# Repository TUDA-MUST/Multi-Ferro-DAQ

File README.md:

# Multi-Ferro-DAQ

**Wearable 8-channel charge amplifier and data acquisition system for piezo- and ferroelectric sensors.**

The system reads up to **8 charge sources simultaneously** via **two RJ45 connectors** (4 sensors per connector).
The PCB is designed for **mobile use**: it can be strapped to a test person, runs on **battery power**, and streams data in **millivolts (mV)** via **Wi-Fi** at up to **2000 samples per second**.

---

## 📋 Specifications

| Parameter | Value |
|---|---|
| Hardware revision | v1.4 |
| Channels | 8, simultaneously sampled |
| ADC | TI ADS131E08, 24 bit ΔΣ, programmable gain G = 1, 2, 4, 8, 12 |
| Charge amplifier | AD8608 (quad CMOS op-amp), one per channel |
| Feedback network | C_F = 680 pF (C0G, ±5 %) ∥ R_F = 1 GΩ (±10 %) |
| Sensitivity | 1 / C_F ≈ 1.47 mV/pC |
| Time constant / lower cut-off | τ = R_F · C_F = 0.68 s → f_c = 1 / (2π τ) ≈ 0.23 Hz |
| Output range (vs. V_bias) | ±2.5 V at G = 1, ±4 V / G for G ≥ 2 |
| Charge range | ±1.70 nC at G = 1 (fault flag above ±2.375 V ≈ ±1.62 nC) |
| Sample rate | 1–2 kSa/s recommended (ADC supports up to 64 kSa/s, but samples are lost above 2 kSa/s) |
| Microcontroller | ESP32-S3-MINI-1-N8 |
| Data interface | Wi-Fi 2.4 GHz access point, TCP port 8080 |
| Power | 1S Li-ion/LiPo (protected cell, JST-PH) or USB-C; on-board charger ≈ 336 mA |
| On-board supplies | 5 V analog (LM2775 charge pump), 3.3 V digital (TPS7A91 LDO), V_bias = 2.5 V |
| Extras | 6-axis IMU (ICM-42670-P), 2 RGB status LEDs, board-level RF shield over the analog front end |
| PCB | 4 layers, 50 mm × 65 mm |

---

## ⚙️ How it works

```mermaid
flowchart LR
    S["Sensors<br/>2 × RJ45, 4 each"] --> CA["8 × charge amplifier<br/>AD8608<br/>C_F = 680 pF ∥ R_F = 1 GΩ"]
    VB["V_bias = 2.5 V<br/>TLV9051 buffer"] --> CA
    VB --> ADC
    CA --> ADC["ADS131E08<br/>8 ch, 24 bit, simultaneous"]
    ADC -- "SPI + DRDY" --> MCU["ESP32-S3"]
    MCU -- "Wi-Fi, TCP :8080" --> PC["Client<br/>MATLAB / MMM"]
    IMU["IMU ICM-42670-P"] -.-> MCU
```

**Analog front end.** The board runs from a single 5 V analog supply. To process bipolar charge signals, all analog circuitry is referenced to a mid-supply voltage **V_bias = 2.5 V**. V_bias is generated by the ADS131E08's internal op-amp and buffered by a TLV9051. Each channel is an inverting charge amplifier: the non-inverting input is tied to V_bias, the inverting input is the summing node the sensor connects to, and C_F ∥ R_F form the feedback. R_F provides the DC path that keeps the output from drifting, and sets the lower cut-off frequency.

**Digitization.** The ADS131E08 samples all eight amplifier outputs simultaneously and measures each one differentially against V_bias, so the result is the amplifier's output voltage relative to mid-supply. The analog front end and the ADC sit under a board-level RF shield.

**Firmware.** The ESP32-S3 uses both cores. An interrupt on the ADC's DRDY signal reads each sample into a queue. A second task converts the raw values to mV, removes the selected PGA gain, and sends packets of 64 samples to the client over TCP.

**Power.** The board runs from a 1S Li-ion/LiPo cell or USB-C. A TP4056 charges the cell from USB. An LM2775 charge pump supplies the 5 V analog rail, and a TPS7A91 low-noise LDO supplies the 3.3 V digital rail.

---

## 🧮 Converting the output to charge

The firmware streams each channel as the amplifier output voltage U (in mV, relative to V_bias, with the PGA gain already removed).
For signal frequencies well above the cut-off f_c ≈ 0.23 Hz, the charge Q delivered by the sensor into the amplifier input is

$$Q = -C_F \cdot U$$

With C_F = 680 pF:

$$Q\,[\mathrm{pC}] = -0.68 \cdot U\,[\mathrm{mV}]$$

Example: U = 100 mV → Q = −68 pC. The amplifier is inverting, so the sign of the output is opposite to the sign of the charge flowing into the input.

The feedback resistor makes the amplifier a high-pass. A charge step decays as e^(−t/τ) with τ = 0.68 s: after 0.68 s only 37 % of the step remains, and after 3.4 s (5τ) less than 1 %. For slow or quasi-static signals, correct for this with the transfer function

$$H(f) = -\frac{1}{C_F} \cdot \frac{j 2\pi f \tau}{1 + j 2\pi f \tau}$$

---

## 🔌 Sensor connection (RJ45 pinout)

Each RJ45 port carries four sensors. Each sensor uses one wire pair: the solid-colored wire goes to the amplifier input (**signal, +**), the striped wire to **V_bias (−)**. Pin numbers follow the jack. Wire colors are given for both T-568A and T-568B, the two wiring schemes for Ethernet cables defined in ANSI/TIA-568. They differ only in that the orange and green pairs are swapped; T-568B is the more common one for commercial installations and patch cables in North America. In both, all odd pins are V_bias (striped wire) and all even pins are signal (solid wire).

**By ADC channel:**

| Port I | Port II | + (signal) pin | T-568A | T-568B | − (V_bias) pin | T-568A | T-568B |
|---|---|---|---|---|---|---|---|
| CHAN1 | CHAN5 | 8 | brown | brown | 7 | white-brown | white-brown |
| CHAN2 | CHAN6 | 6 | orange | green | 3 | white-orange | white-green |
| CHAN3 | CHAN7 | 2 | green | orange | 1 | white-green | white-orange |
| CHAN4 | CHAN8 | 4 | blue | blue | 5 | white-blue | white-blue |

**By RJ45 pin:**

| Pin | Wire (T-568A) | Wire (T-568B) | Port I | Port II |
|---|---|---|---|---|
| 1 | white-green | white-orange | CHAN3 − | CHAN7 − |
| 2 | green | orange | CHAN3 + | CHAN7 + |
| 3 | white-orange | white-green | CHAN2 − | CHAN6 − |
| 4 | blue | blue | CHAN4 + | CHAN8 + |
| 5 | white-blue | white-blue | CHAN4 − | CHAN8 − |
| 6 | orange | green | CHAN2 + | CHAN6 + |
| 7 | white-brown | white-brown | CHAN1 − | CHAN5 − |
| 8 | brown | brown | CHAN1 + | CHAN5 + |

> **Important:** the V_bias pins sit at **2.5 V above board ground**. Never connect them to GND or to the cable shield. Shorting V_bias to ground loads the reference and drives the channels into saturation. Use the RJ45 shield for the cable screen. It connects to the board's shield net.

The pinout is also printed on the PCB silkscreen (T-568B colors).

---

## 🛠️ Building the hardware

1. **Order the PCB with assembly** (e.g. JLCPCB) using the files in [`PCB/jlcpcb/production_files`](PCB/jlcpcb/production_files): Gerber archive, BOM and CPL.
   - 4-layer board, stackup JLC041611-3313, 1 oz inner copper (see `PCB/jlcpcb/Added Info.txt`).
2. **Order separately** (not part of the assembly BOM):
   - Laird **BMI-S-204-C** RF shield cover.
   - A **protected** 1S Li-ion/LiPo cell with a JST-PH 2-pin plug. The on-board TP4056 charger has no cell protection.
   - RJ45 cables or adapters for your sensors.
3. **After assembly:**
   - Press the shield cover onto the soldered J7 frame.
   - Check the solder jumpers. The factory states are listed in the BOM documentation.
   - Connect the battery and flash the firmware (see below).

The complete bill of materials, with manufacturer part numbers, key specs and datasheet links, is in [`PCB/BOM`](PCB/BOM/README.md) ([CSV](PCB/BOM/BOM_Multi-Ferro-DAQ_v1.4.csv)). The design files require **KiCad 10**. All project-specific symbols, footprints and 3D models are in `PCB/components`.

---

## ⚡ Flashing the firmware

The ESP32-S3 is flashed with the Arduino IDE using
`Software/ADC_readout/ardu_adc_dual_core_wifi_tcp/ardu_adc_dual_core_wifi_tcp.ino`.
The sketch includes the driver from `Software/ADC_readout/lib/`, so keep the folder structure intact.

**Required:**
- Arduino-ESP32 core (Espressif), installed via the Boards Manager
- FastLED library
- ArduinoJson library (only for the MultiMeasurementMonitor firmware)

**Board settings** (Tools menu):

| Setting | Value |
|---|---|
| Board | Adafruit Feather ESP32-S3 No PSRAM |
| USB CDC On Boot | Enabled |
| CPU Frequency | 240 MHz (WiFi) |
| Events Run On | **Core 0** |
| Arduino Runs On | **Core 0** |
| Flash Mode | QIO 80 MHz |
| Flash Size | 8 MB (64 Mb) |
| Partition Scheme | TinyUF2 8MB (2MB APP/3.7MB FATFS) |
| Upload Mode | USB-OTG CDC (TinyUSB) |
| USB Mode | USB-OTG (TinyUSB) |

For the first flash, or if the upload fails, put the ESP32 into programming mode: press and hold **BOOT**, briefly press **RESET**, then release BOOT. The ESP32 is then detected automatically, or can be selected as an "ESP32 Family Device" under the port selection.

Only enter programming mode after a compile/upload for the board above has started. Otherwise the IDE tries, and fails, to build for an "ESP32 Family Device".

The firmware is tested with the MATLAB script [`Software/ADC_readout/Matlab/ADC_WiFi_readout_TCP.m`](Software/ADC_readout/Matlab/ADC_WiFi_readout_TCP.m) using MATLAB R2024b.

---

## 🧩 Setup

### 1. Power On
- Flip the power switch to **ON**, or **reset** the powered-on PCB.
- During startup, the **status LED** turns **YELLOW**, indicating the setup phase.

### 2. Ready State
- When the LED turns **MAGENTA**, the ESP32 is ready to start a measurement.
- A **white flash** under the shielding of the charge amplifiers and ADC indicates that the ADC is set up and communicating.

### 3. Wi-Fi Connection
Connect to the ESP32's Wi-Fi hotspot:

- SSID: `ESP32_Hotspot`
- Password: `123456789`

Then connect to **IP address 192.168.4.1** on **TCP port 8080**
(see this [MATLAB script](Software/ADC_readout/Matlab/ADC_WiFi_readout_TCP.m) for details).

> The hotspot credentials are hard-coded in the firmware. Change them in the sketch if the board is used outside the lab.

### 4. Initialization
The ESP32 expects initialization values in a **fixed format and order** (36 bytes, little-endian).
Garbage bytes can be sent to initialize with the ADC's own default values.

| Data Type | Count | Description |
|------------|--------|-------------|
| `int64` | 1 | Maximum number of samples to collect (PCB resets afterwards). |
| `uint32` | 1 | ADC sample rate. Choose from `1000, 2000, 4000, 8000, 16000, 32000, 64000`. <br>Rates above **2000** cause sample loss and are **not recommended**. |
| `uint16` | 8 | ADC settings registers for **CHAN1–CHAN8**. <br>Only the lower byte is used; set the upper byte to zero. |
| `uint8` | 8 | PGA gain for **CHAN1–CHAN8** (1, 2, 4, 8 or 12). <br>These overwrite the gain previously set in the settings registers. The microcontroller removes the gain before transmitting the data. |

### 5. Start Measurement
Once initialized, the **status LED turns GREEN**. It stays green until:
- the measurement **times out**, or
- it is **stopped** manually.

---

## 🔋 Power Supply

- The PCB can be powered via **USB-C** or the **battery port**.
- The battery is **charged directly by the PCB**.

**Battery indicator LED:**
- **Solid RED:** battery is charging.
- **Fast blinking RED (while powered on):** no battery detected.

---

## 📡 Usage

After setup, the microcontroller sends data via **TCP** to the client until:
- the measurement **times out**, or
- it is **stopped** by the client sending **any byte** via TCP.

### Data Output Format

The TCP stream consists of samples of **nine little-endian `float32` values** (36 bytes per sample), sent in packets of 64 samples (2304 bytes):

| Channel | Description |
|----------|--------------|
| **CHAN1–CHAN8** | Amplifier output in mV relative to V_bias (`–2500 mV` to `+2500 mV`). See [Converting the output to charge](#-converting-the-output-to-charge). |
| **CHAN9** | Timestamp in µs since the last ESP32 reset |

**Fault Flags:**
- A value of `–9999 mV` or `+9999 mV` means the ADC's **negative or positive fault flag** was triggered.
  This happens when the measured value exceeds **±2375 mV** (≈ 95 % of the input range).

**Timestamp resolution:** the timestamp is transmitted as `float32`, so its resolution decreases with time since reset. The step size is 2 µs after 16.8 s, 64 µs after 9 min, and 512 µs after 71.6 min. Reset the board before long measurements if exact sample timing matters.

---

## 📡 Usage with MultiMeasurementMonitor

The DAQ can also be used as a client for the MMM (MultiMeasurementMonitor) project with this [firmware](Software/MMM_Migration).

The available settings stay the same, but you get the benefits of the MMM. The ClientName is set via the JSON file when programming, and the Wi-Fi credentials can be changed via the Serial Monitor at startup.

For further details on using clients with the MMM, see the [MMM project on GitHub](https://github.com/TUDA-MUST/Multi-Measurement-Monitor).

---

## 🔁 Post-Measurement

- After a measurement ends, the PCB **automatically reinitializes**.
- It is ready again when the **status LED turns MAGENTA**.
- The PCB can also be **reinitialized manually** by pressing **RESET**.

---

## 🧭 Additional Features

- An **IMU** (ICM-42670-P) is included on the PCB.
  It has been tested, but is **not used** by the current firmware.

---

## 📄 License

| Content | License |
|---|---|
| Hardware (PCB design and production files) | [CERN-OHL-W-2.0](LICENSES/CERN-OHL-W-2.0.txt) |
| Software (firmware, scripts) | [MIT](LICENSES/MIT.txt) |
| Documentation and images | [CC BY 4.0](LICENSES/CC-BY-4.0.txt) |

Copyright (c) 2024–2026 Measurement and Sensor Technology Group (MUST), TU Darmstadt and contributors.
See [LICENSE](LICENSE) for details and [THIRD_PARTY_NOTICES.md](THIRD_PARTY_NOTICES.md) for third-party components.

## 📝 Citation

If you use Multi-Ferro-DAQ in your research, please cite it using the metadata in [CITATION.cff](CITATION.cff) (GitHub: "Cite this repository").

---

## 🙏 Acknowledgements

- The ADS131E08 driver is based on the [ads131e08](https://github.com/mcjun37/ads131e08) STM32 library by **Minchul Jun**,
  ported to the ESP32 by **Thomas Schreck**. See [THIRD_PARTY_NOTICES.md](THIRD_PARTY_NOTICES.md) for its license.

Developed at the [Measurement and Sensor Technology Group (MUST)](https://www.etit.tu-darmstadt.de/must/), Technische Universität Darmstadt.

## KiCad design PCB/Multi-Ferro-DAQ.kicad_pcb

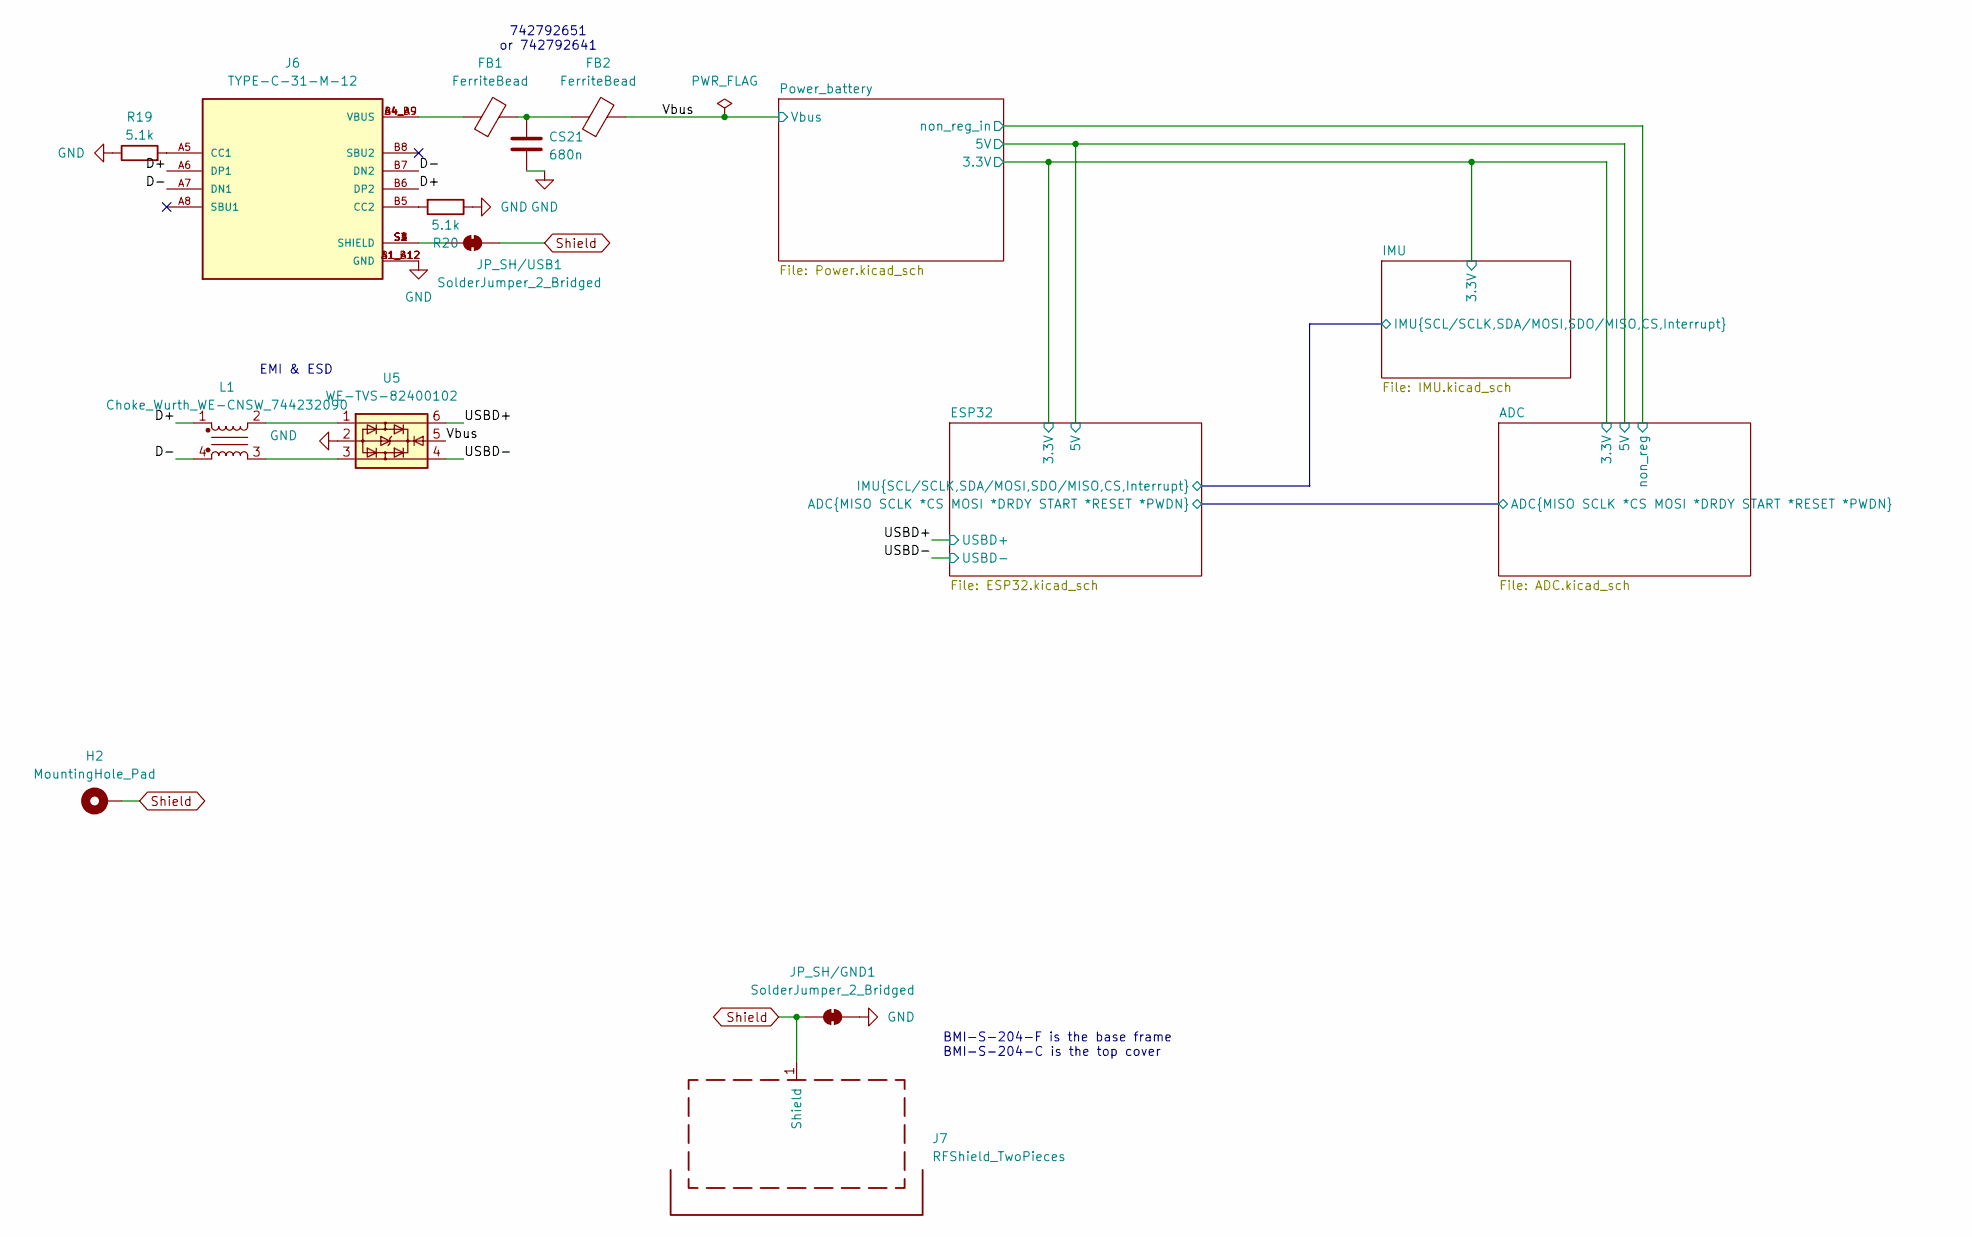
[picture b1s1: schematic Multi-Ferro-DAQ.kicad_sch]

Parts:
CS21: 680n; C_0603_1608Metric; LCSC C5360852
FB1, FB2: FerriteBead; L_0603_1608Metric; LCSC C2649308
H2: MountingHole_Pad; MountingHole_3.2mm_M3_Pad; LCSC C5221843
J6: TYPE-C-31-M-12; HRO_TYPE-C-31-M-12; PARTREV 2020.12.08; LCSC C165948
J7: RFShield_TwoPieces; Laird_Technologies_BMI-S-204-F_32.00x32.00mm; LCSC C5241024
JP_SH/GND1: SolderJumper_2_Bridged; SolderJumper-2_P1.3mm_Bridged2Bar_RoundedPad1.0x1.5mm
JP_SH/USB1: SolderJumper_2_Bridged; SolderJumper-2_P1.3mm_Bridged2Bar_RoundedPad1.0x1.5mm
L1: Choke_Wurth_WE-CNSW_744232090; L_CommonMode_Wurth_WE-CNSW-1206; LCSC C2649327
R19, R20: 5.1k; R_0603_1608Metric; LCSC C23186
U5: WE-TVS-82400102; SOT-23-6; LCSC C1975330

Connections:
/D+: J6.A6 (DP1), J6.B6 (DP2), L1.1
/D-: J6.A7 (DN1), J6.B7 (DN2), L1.4
/USBD+: U5.6; also elsewhere on the board
/USBD-: U5.4; also elsewhere on the board
/Vbus: FB2.2, U5.5; also elsewhere on the board
GND: CS21.1, J6.A1_B12 (GND), J6.B1_A12 (GND), JP_SH/GND1.2 (B), R19.1, R20.1, U5.2; also elsewhere on the board
unnamed: CS21.2, FB1.2, FB2.1
unnamed: FB1.1, J6.A4_B9 (VBUS), J6.B4_A9 (VBUS)
unnamed: J6.A5 (CC1), R19.2
unnamed: J6.B5 (CC2), R20.2
unnamed: J6.S1 (SHIELD), J6.S2 (SHIELD), J6.S3 (SHIELD), J6.S4 (SHIELD), JP_SH/USB1.1 (A)
unnamed: L1.2, U5.1
unnamed: L1.3, U5.3
Shield: H2.1 (1_1), J7.1 (Shield_1), JP_SH/GND1.1 (A), JP_SH/USB1.2 (B); also elsewhere on the board

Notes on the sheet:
BMI-S-204-F is the base frame BMI-S-204-C is the top cover
742792651 or 742792641
EMI & ESD

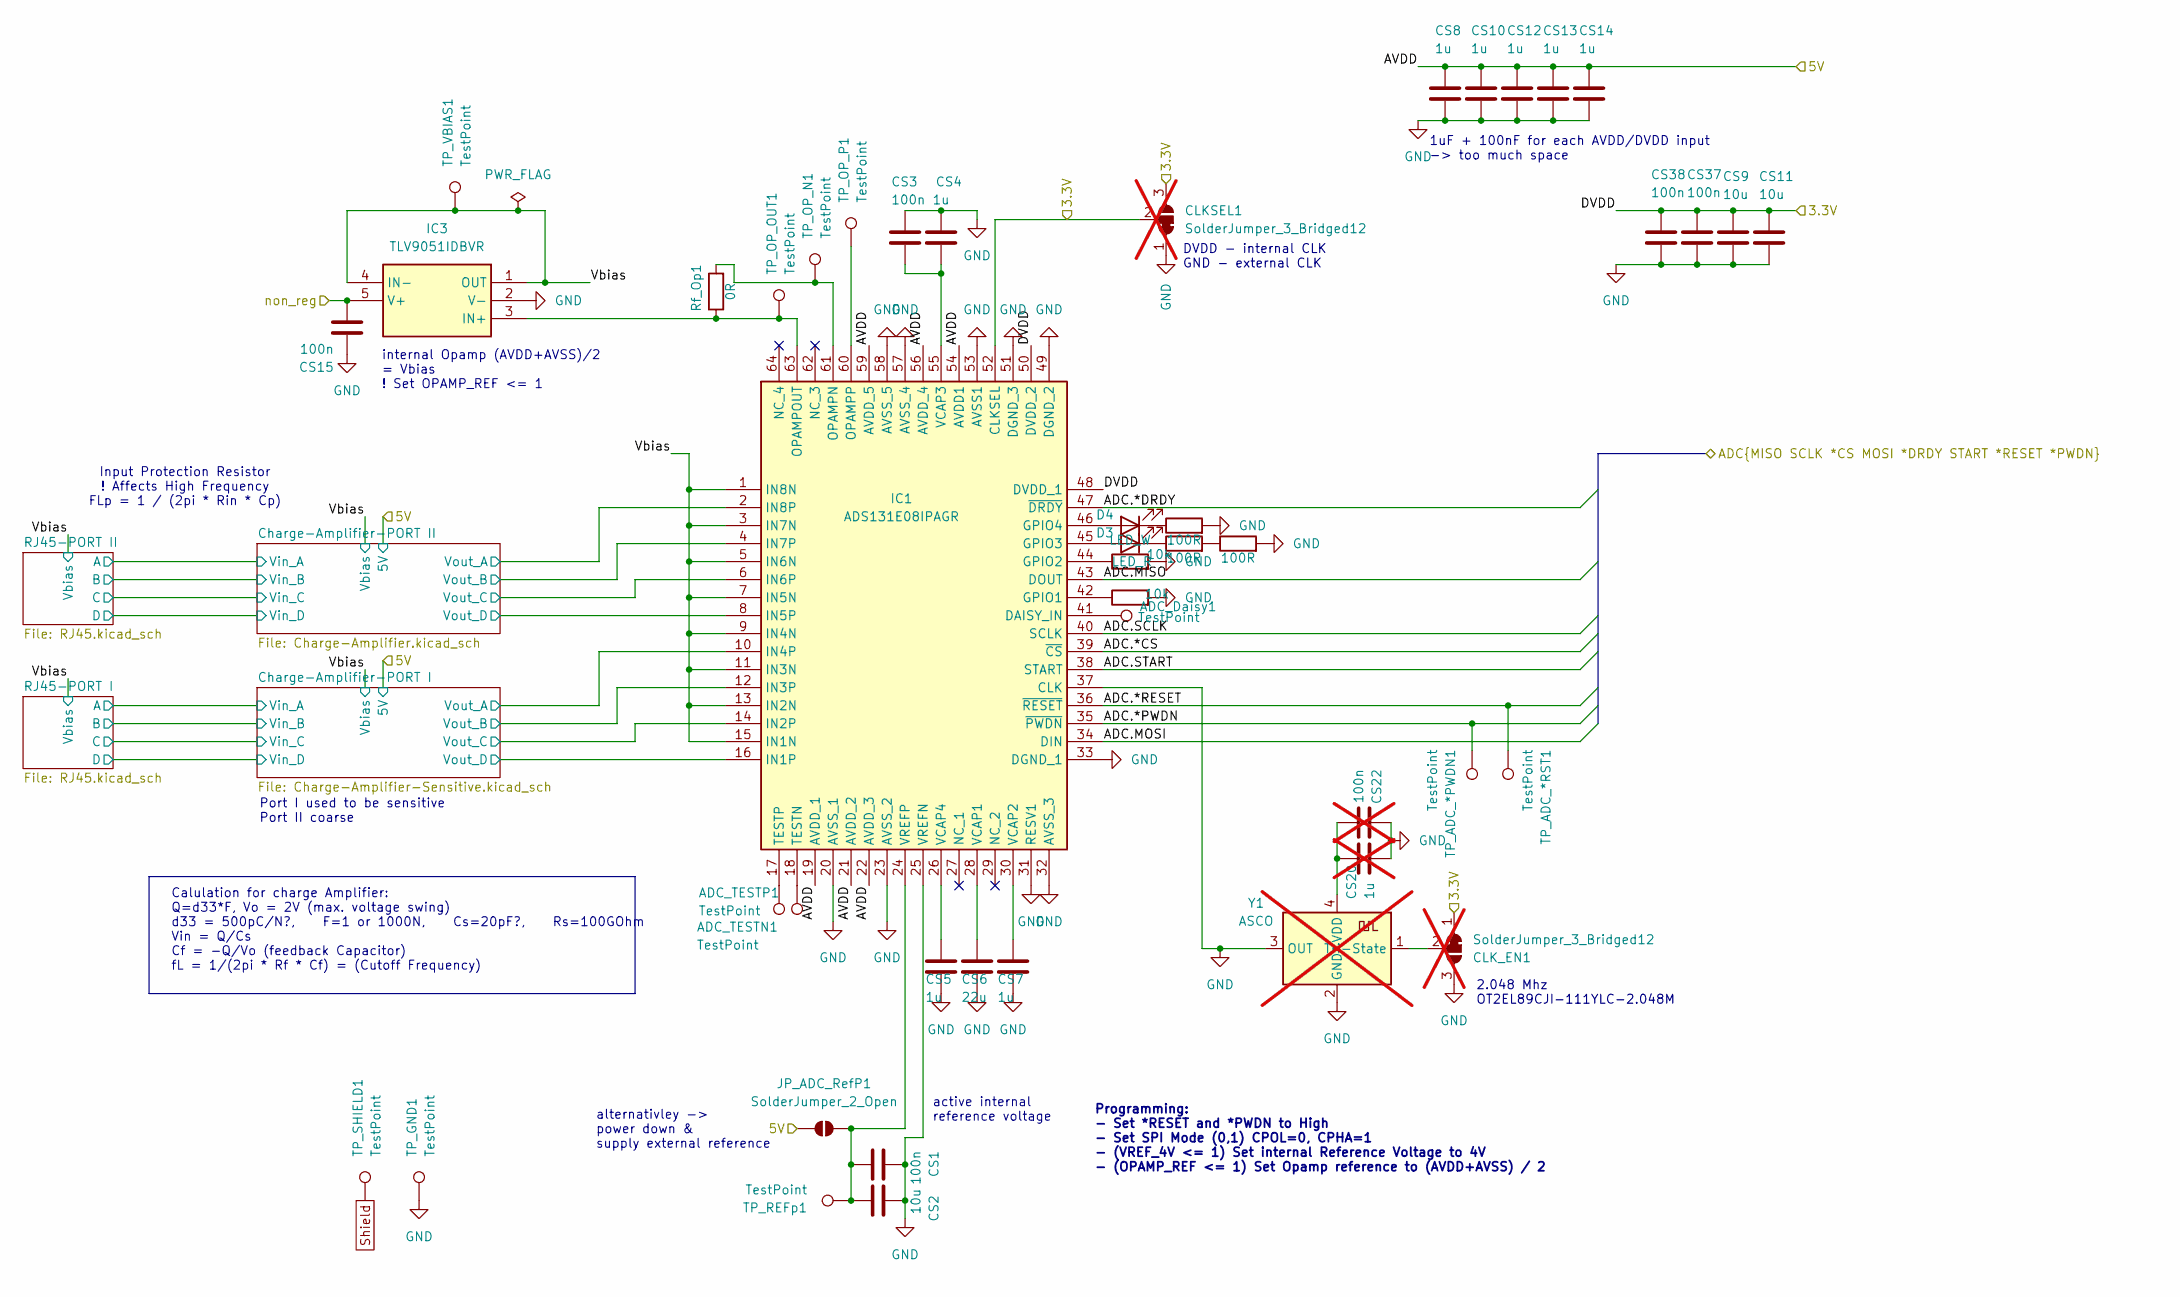
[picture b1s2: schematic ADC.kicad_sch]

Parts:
ADC_Daisy1: TestPoint; TestPoint_Pad_D1.0mm
ADC_TESTN1: TestPoint; TestPoint_Pad_D1.0mm
ADC_TESTP1: TestPoint; TestPoint_Pad_D1.0mm
CLKSEL1: SolderJumper_3_Bridged12; SolderJumper-3_P1.3mm_Bridged2Bar12_RoundedPad1.0x1.5mm; not fitted
CLK_EN1: SolderJumper_3_Bridged12; SolderJumper-3_P1.3mm_Bridged2Bar12_RoundedPad1.0x1.5mm; not fitted
CS1, CS3, CS15, CS37, CS38: 100n; C_0603_1608Metric; LCSC C14663
CS2, CS9, CS11: 10u; C_0603_1608Metric; LCSC C19702
CS4, CS5, CS7, CS8, CS10, CS12, CS13, CS14: 1u; C_0603_1608Metric; LCSC C15849
CS6: 22u; C_0603_1608Metric; LCSC C59461
CS20: 1u; C_0603_1608Metric; not fitted
CS22: 100n; C_0603_1608Metric; not fitted
D3: LED_R; LED_0603_1608Metric; LCSC C2286
D4: LED_W; LED_0603_1608Metric; LCSC C2290
IC1: ADS131E08IPAGR; QFP50P1200X1200X120-64N; Mouser Part Number 595-ADS131E08IPAGR
IC3: TLV9051IDBVR; SOT95P280X145-5N; Mouser Part Number 595-TLV9051IDBVR
JP_ADC_RefP1: SolderJumper_2_Open; SolderJumper-2_P1.3mm_Open_RoundedPad1.0x1.5mm
R1, R2: 10k; R_0603_1608Metric; LCSC C25804
R3, R4, R5: 100R; R_0603_1608Metric; LCSC C22775
Rf_Op1: 0R; R_0603_1608Metric; LCSC C21189
TP_ADC_*PWDN1: TestPoint; TestPoint_Pad_D1.0mm
TP_ADC_*RST1: TestPoint; TestPoint_Pad_D1.0mm
TP_GND1: TestPoint; TestPoint_Pad_D1.0mm
TP_OP_N1: TestPoint; TestPoint_Pad_D1.0mm
TP_OP_OUT1: TestPoint; TestPoint_Pad_D1.0mm
TP_OP_P1: TestPoint; TestPoint_Pad_D1.0mm
TP_REFp1: TestPoint; TestPoint_Pad_D1.0mm
TP_SHIELD1: TestPoint; TestPoint_Pad_D1.0mm
TP_VBIAS1: TestPoint; TestPoint_Pad_D1.0mm
Y1: ASCO; Crystal_SMD_3225-4Pin_3.2x2.5mm; not fitted

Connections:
/ADC/ADC.*CS: IC1.39 (~CS); also elsewhere on the board
/ADC/ADC.*DRDY: IC1.47 (~DRDY); also elsewhere on the board
/ADC/ADC.*PWDN: IC1.35 (~PWDN), TP_ADC_*PWDN1.1 (1_1); also elsewhere on the board
/ADC/ADC.*RESET: IC1.36 (~RESET), TP_ADC_*RST1.1 (1_1); also elsewhere on the board
/ADC/ADC.MISO: IC1.43 (DOUT); also elsewhere on the board
/ADC/ADC.MOSI: IC1.34 (DIN); also elsewhere on the board
/ADC/ADC.SCLK: IC1.40 (SCLK); also elsewhere on the board
/ADC/ADC.START: IC1.38 (START); also elsewhere on the board
/ADC/AVDD: CS8.2, CS10.2, CS12.2, CS13.2, CS14.2, IC1.19 (AVDD_1), IC1.21 (AVDD_2), IC1.22 (AVDD_3), IC1.54 (AVDD1), IC1.56 (AVDD_4), IC1.59 (AVDD_5), JP_ADC_RefP1.1 (A); also elsewhere on the board
/ADC/Charge-Amplifier-PORT I/Vout_A: IC1.10 (IN4P); also elsewhere on the board
/ADC/Charge-Amplifier-PORT I/Vout_B: IC1.12 (IN3P); also elsewhere on the board
/ADC/Charge-Amplifier-PORT I/Vout_C: IC1.14 (IN2P); also elsewhere on the board
/ADC/Charge-Amplifier-PORT I/Vout_D: IC1.16 (IN1P); also elsewhere on the board
/ADC/Charge-Amplifier-PORT II/Vout_A: IC1.2 (IN8P); also elsewhere on the board
/ADC/Charge-Amplifier-PORT II/Vout_B: IC1.4 (IN7P); also elsewhere on the board
/ADC/Charge-Amplifier-PORT II/Vout_C: IC1.6 (IN6P); also elsewhere on the board
/ADC/Charge-Amplifier-PORT II/Vout_D: IC1.8 (IN5P); also elsewhere on the board
/ADC/DVDD: CLKSEL1.2 (C), CLKSEL1.3 (B), CLK_EN1.1 (A), CS9.2, CS11.2, CS37.2, CS38.2, IC1.48 (DVDD_1), IC1.50 (DVDD_2), IC1.52 (CLKSEL); also elsewhere on the board
/ADC/Vbias: IC1.1 (IN8N), IC1.3 (IN7N), IC1.5 (IN6N), IC1.7 (IN5N), IC1.9 (IN4N), IC1.11 (IN3N), IC1.13 (IN2N), IC1.15 (IN1N), IC3.1 (OUT), IC3.4 (IN-), TP_VBIAS1.1 (1_1); also elsewhere on the board
/Power_battery/non_reg_in: CS15.1, IC3.5 (V+); also elsewhere on the board
GND: CLKSEL1.1 (A), CLK_EN1.3 (B), CS1.2, CS2.2, CS3.2, CS4.1, CS5.2, CS6.2, CS7.2, CS8.1, CS9.1, CS10.1, CS11.1, CS12.1, CS13.1, CS14.1, CS15.2, CS20.2, CS22.2, CS37.1, CS38.1, IC1.20 (AVSS_1), IC1.23 (AVSS_2), IC1.25 (VREFN), IC1.31 (RESV1), IC1.32 (AVSS_3), IC1.33 (DGND_1), IC1.37 (CLK), IC1.49 (DGND_2), IC1.51 (DGND_3), IC1.53 (AVSS1), IC1.57 (AVSS_4), IC1.58 (AVSS_5), IC3.2 (V-), R1.2, R2.2, R3.2, R5.2, TP_GND1.1 (1_1), Y1.2 (GND), Y1.3 (OUT); also elsewhere on the board
unnamed: CLK_EN1.2 (C), Y1.1 (Tri-State)
unnamed: CS20.1, CS22.1, Y1.4 (VDD)
unnamed: D3.2 (A), IC1.45 (GPIO3)
unnamed: D3.1 (K), R4.1
unnamed: D4.2 (A), IC1.46 (GPIO4)
unnamed: D4.1 (K), R3.1
unnamed: ADC_Daisy1.1 (1_1), IC1.41 (DAISY_IN)
unnamed: IC1.42 (GPIO1), R2.1
unnamed: IC1.44 (GPIO2), R1.1
unnamed: IC1.61 (OPAMPN), Rf_Op1.2, TP_OP_N1.1 (1_1)
unnamed: IC1.63 (OPAMPOUT), IC3.3 (IN+), Rf_Op1.1, TP_OP_OUT1.1 (1_1)
unnamed: IC1.60 (OPAMPP), TP_OP_P1.1 (1_1)
unnamed: ADC_TESTN1.1 (1_1), IC1.18 (TESTN)
unnamed: ADC_TESTP1.1 (1_1), IC1.17 (TESTP)
unnamed: CS6.1, IC1.28 (VCAP1)
unnamed: CS7.1, IC1.30 (VCAP2)
unnamed: CS3.1, CS4.2, IC1.55 (VCAP3)
unnamed: CS5.1, IC1.26 (VCAP4)
unnamed: CS1.1, CS2.1, IC1.24 (VREFP), JP_ADC_RefP1.2 (B), TP_REFp1.1 (1_1)
unnamed: R4.2, R5.1
Shield: TP_SHIELD1.1 (1_1); also elsewhere on the board

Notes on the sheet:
active internal reference voltage
Input Protection Resistor ! Affects High Frequency FLp = 1 / (2pi * Rin * Cp)
1uF + 100nF for each AVDD/DVDD input -> too much space
DVDD - internal CLK GND - external CLK
alternativley -> power down & supply external reference
2.048 Mhz OT2EL89CJI-111YLC-2.048M
Calulation for charge Amplifier: Q=d33*F, Vo = 2V (max. voltage swing) d33 = 500pC/N?, F=1 or 1000N, Cs=20pF?, Rs=100GOhm Vin = Q/Cs Cf = -Q/Vo (feedback Capacitor) fL = 1/(2pi * Rf * Cf) = (Cutoff Frequency)
Programming: - Set *RESET and *PWDN to High - Set SPI Mode (0,1) CPOL=0, CPHA=1 - (VREF_4V <= 1) Set internal Reference Voltage to 4V - (OPAMP_REF <= 1) Set Opamp reference to (AVDD+AVSS) / 2
internal Opamp (AVDD+AVSS)/2 = Vbias ! Set OPAMP_REF <= 1
Port I used to be sensitive Port II coarse

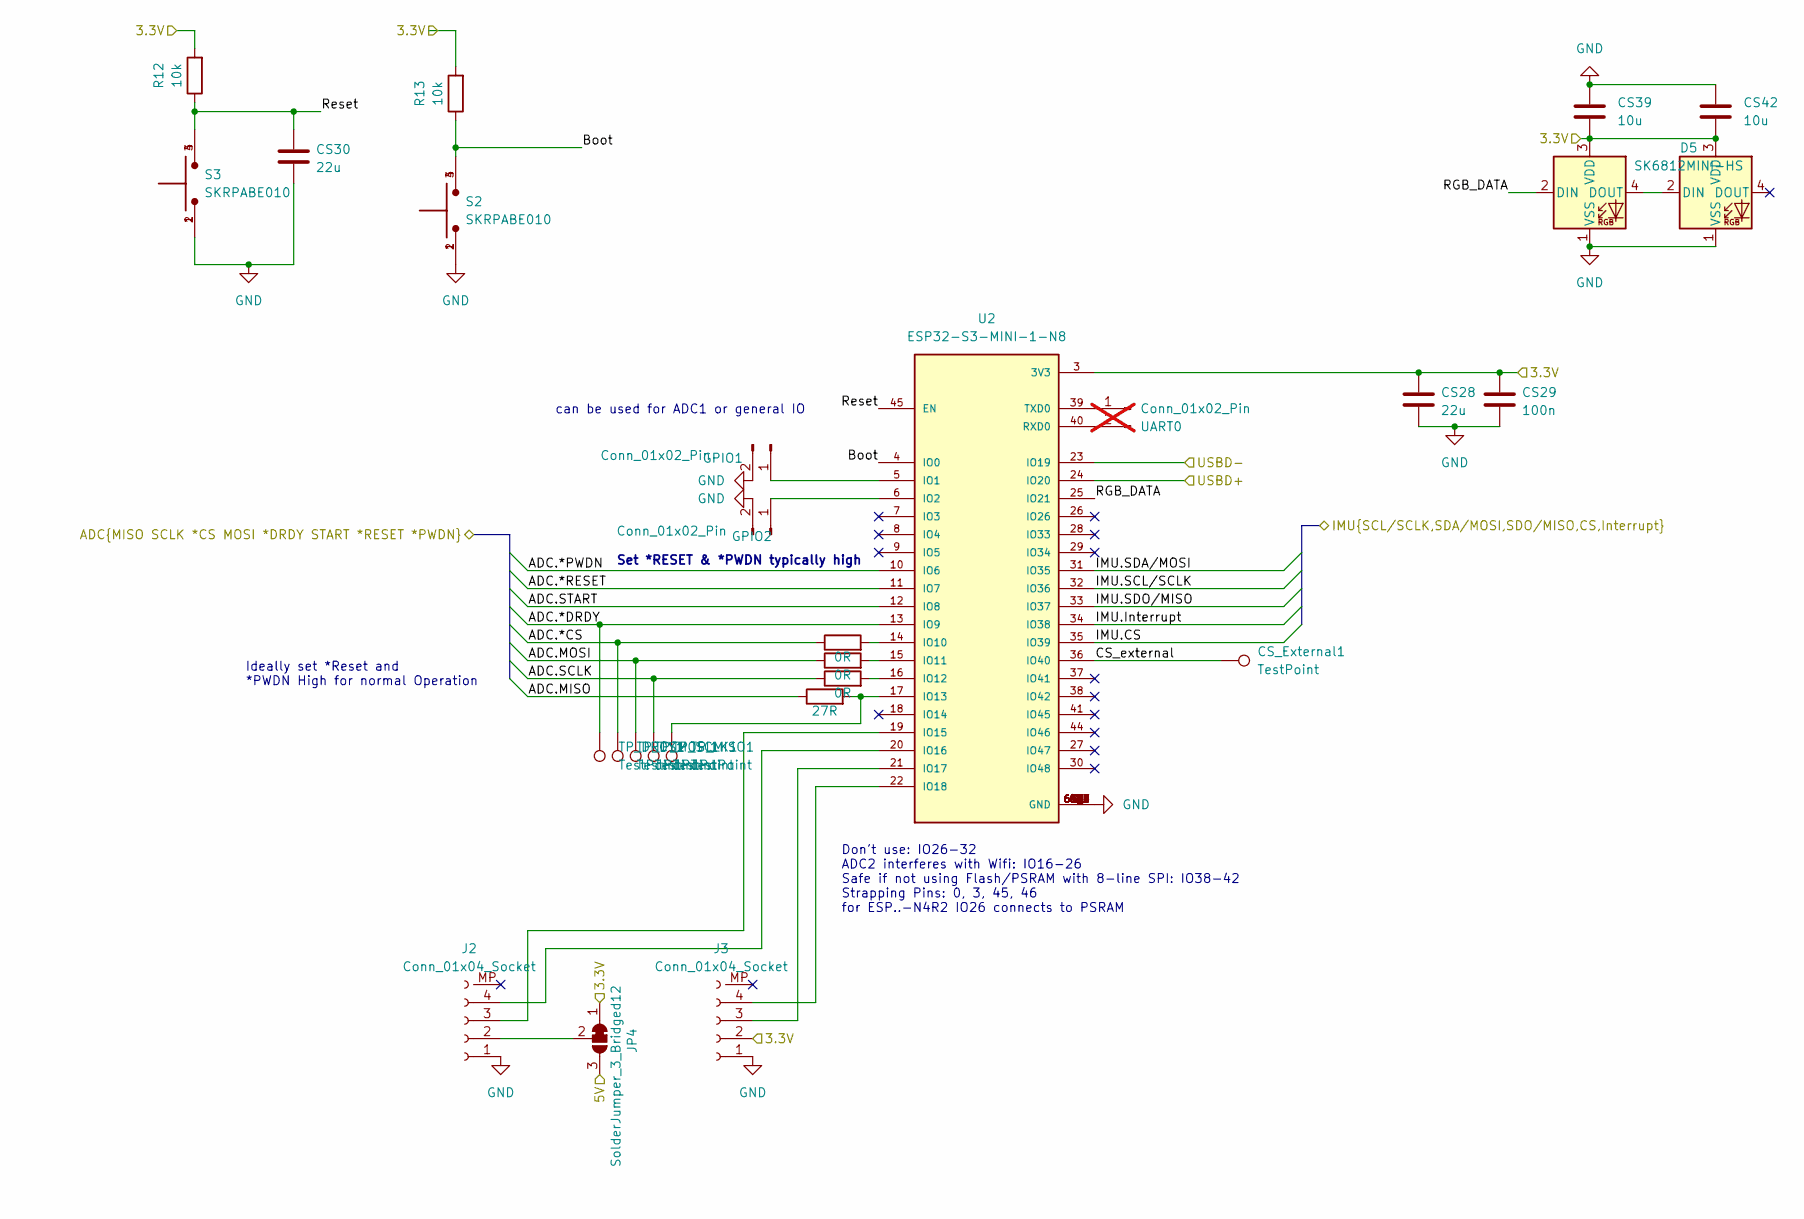
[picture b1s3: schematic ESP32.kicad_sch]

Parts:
CS28, CS30: 22u; C_0603_1608Metric; LCSC C59461
CS29: 100n; C_0603_1608Metric; LCSC C14663
CS39, CS42: 10u; C_0603_1608Metric; LCSC C19702
CS_External1: TestPoint; TestPoint_THTPad_D1.0mm_Drill0.5mm
D5, D6: SK6812MINI-HS; SK6812MNI-HS; LCSC C2922787
GPIO1, GPIO2: Conn_01x02_Pin; PinHeader_1x02_P2.54mm_Vertical; LCSC C492401
J2, J3: Conn_01x04_Socket; JST_SH_BM04B-SRSS-TB_1x04-1MP_P1.00mm_Vertical; LCSC C495539
JP4: SolderJumper_3_Bridged12; SolderJumper-3_P1.3mm_Bridged2Bar12_RoundedPad1.0x1.5mm
R12, R13: 10k; R_0603_1608Metric; LCSC C25804
R27: 27R; R_0603_1608Metric; LCSC C25190
R28, R29, R30: 0R; R_0603_1608Metric; LCSC C21189
S2, S3: SKRPABE010; SW_SKRPABE010; LCSC C115360
TP_CS1: TestPoint; TestPoint_Pad_D1.0mm
TP_DRDY1: TestPoint; TestPoint_Pad_D1.0mm
TP_MISO1: TestPoint; TestPoint_Pad_D1.0mm
TP_MOSI1: TestPoint; TestPoint_Pad_D1.0mm
TP_SCLK1: TestPoint; TestPoint_Pad_D1.0mm
U2: ESP32-S3-MINI-1-N8; XCVR_ESP32-S3-MINI-1-N8; PARTREV v0.6; LCSC C2913206
UART0: Conn_01x02_Pin; PinHeader_1x02_P1.27mm_Vertical; not fitted

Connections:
/ADC/ADC.*CS: R30.1, TP_CS1.1 (1_1); also elsewhere on the board
/ADC/ADC.*DRDY: TP_DRDY1.1 (1_1), U2.13 (IO9); also elsewhere on the board
/ADC/ADC.*PWDN: U2.10 (IO6); also elsewhere on the board
/ADC/ADC.*RESET: U2.11 (IO7); also elsewhere on the board
/ADC/ADC.MISO: R27.1; also elsewhere on the board
/ADC/ADC.MOSI: R28.1, TP_MOSI1.1 (1_1); also elsewhere on the board
/ADC/ADC.SCLK: R29.1, TP_SCLK1.1 (1_1); also elsewhere on the board
/ADC/ADC.START: U2.12 (IO8); also elsewhere on the board
/ADC/AVDD: JP4.3 (B); also elsewhere on the board
/ADC/DVDD: CS28.2, CS29.2, CS39.1, CS42.1, D5.3 (VDD), D6.3 (VDD), J3.2, JP4.1 (A), R12.2, R13.2, U2.3 (3V3); also elsewhere on the board
/ESP32/Boot: R13.1, S2.3, S2.4, U2.4 (IO0)
/ESP32/CS_external: CS_External1.1 (1_1), U2.36 (IO40)
/ESP32/IMU.CS: U2.35 (IO39); also elsewhere on the board
/ESP32/IMU.Interrupt: U2.34 (IO38); also elsewhere on the board
/ESP32/IMU.SCL/SCLK: U2.32 (IO36); also elsewhere on the board
/ESP32/IMU.SDA/MOSI: U2.31 (IO35); also elsewhere on the board
/ESP32/IMU.SDO/MISO: U2.33 (IO37); also elsewhere on the board
/ESP32/RGB_DATA: D5.2 (DIN), U2.25 (IO21)
/ESP32/Reset: CS30.2, R12.1, S3.3, S3.4, U2.45 (EN)
/USBD+: U2.24 (IO20); also elsewhere on the board
/USBD-: U2.23 (IO19); also elsewhere on the board
GND: CS28.1, CS29.1, CS30.1, CS39.2, CS42.2, D5.1 (VSS), D6.1 (VSS), GPIO1.2, GPIO2.2, J2.1, J3.1, S2.1, S2.2, S3.1, S3.2, U2.1 (GND), U2.2 (GND), U2.42 (GND), U2.43 (GND), U2.46 (GND), U2.47 (GND), U2.48 (GND), U2.49 (GND), U2.50 (GND), U2.51 (GND), U2.52 (GND), U2.53 (GND), U2.54 (GND), U2.55 (GND), U2.56 (GND), U2.57 (GND), U2.58 (GND), U2.59 (GND), U2.60 (GND), U2.61 (GND), U2.61_1 (GND), U2.61_2 (GND), U2.61_3 (GND), U2.61_4 (GND), U2.61_5 (GND), U2.61_6 (GND), U2.61_7 (GND), U2.61_8 (GND), U2.62 (GND), U2.63 (GND), U2.64 (GND), U2.65 (GND); also elsewhere on the board
unnamed: D5.4 (DOUT), D6.2 (DIN)
unnamed: GPIO1.1, U2.5 (IO1)
unnamed: GPIO2.1, U2.6 (IO2)
unnamed: J2.2, JP4.2 (C)
unnamed: J2.3, U2.19 (IO15)
unnamed: J3.3, U2.21 (IO17)
unnamed: R30.2, U2.14 (IO10)
unnamed: R28.2, U2.15 (IO11)
unnamed: R29.2, U2.16 (IO12)
unnamed: R27.2, TP_MISO1.1 (1_1), U2.17 (IO13)
unnamed: J2.4, U2.20 (IO16)
unnamed: J3.4, U2.22 (IO18)
unnamed: U2.40 (RXD0), UART0.2
unnamed: U2.39 (TXD0), UART0.1

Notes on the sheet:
Don't use: IO26-32 ADC2 interferes with Wifi: IO16-26 Safe if not using Flash/PSRAM with 8-line SPI: IO38-42 Strapping Pins: 0, 3, 45, 46 for ESP..-N4R2 IO26 connects to PSRAM
Set *RESET & *PWDN typically high
Ideally set *Reset and *PWDN High for normal Operation
can be used for ADC1 or general IO

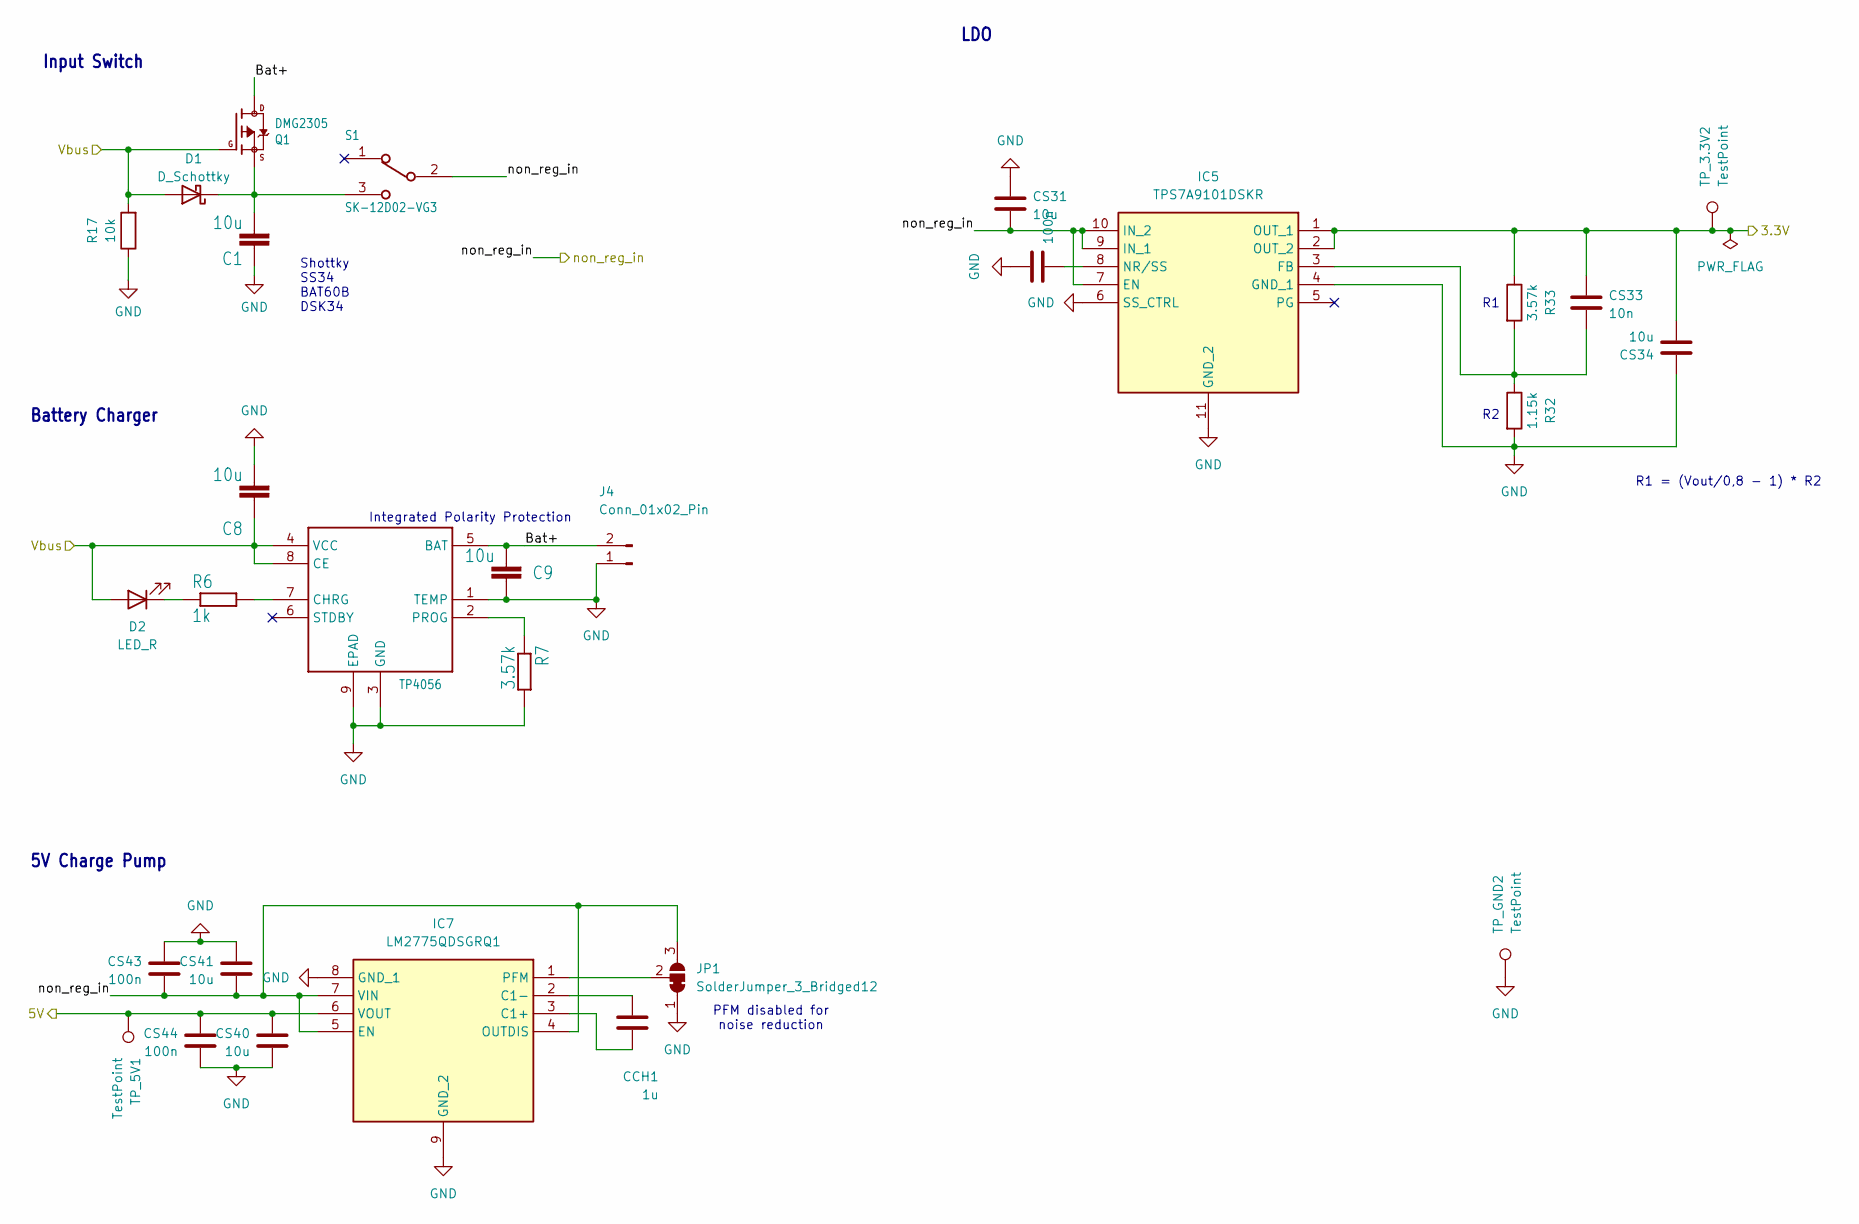
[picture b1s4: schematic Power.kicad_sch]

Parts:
C1, C8, C9: 10u; C_0603_1608Metric; LCSC C19702
CCH1: 1u; C_0603_1608Metric; LCSC C15849
CS31, CS34, CS40, CS41: 10u; C_0603_1608Metric; LCSC C19702
CS32, CS43, CS44: 100n; C_0603_1608Metric; LCSC C14663
CS33: 10n; C_0603_1608Metric; LCSC C57112
D1: D_Schottky; D_SOD-323; LCSC C7502695
D2: LED_R; LED_0603_1608Metric; LCSC C2286
IC2: TP4056; SOP127P600X175-9N; LCSC C2763448
IC5: TPS7A9101DSKR; SON50P250X250X80-11N-D; Mouser Part Number 595-TPS7A9101DSKR
IC7: LM2775QDSGRQ1; SON50P200X200X80-9N; Mouser Part Number 595-LM2775QDSGRQ1
J4: Conn_01x02_Pin; JST_PH_B2B-PH-K_1x02_P2.00mm_Vertical; LCSC C594142
JP1: SolderJumper_3_Bridged12; SolderJumper-3_P1.3mm_Bridged2Bar12_RoundedPad1.0x1.5mm
Q1: DMG2305; DMG2305UX; LCSC C2940629
R6: 1k; R_0603_1608Metric; LCSC C21190
R7, R33: 3.57k; R_0603_1608Metric; LCSC C326745
R17: 10k; R_0603_1608Metric; LCSC C25804
R32: 1.15k; R_0603_1608Metric; LCSC C861724
S1: SK-12D02-VG3; SK12D02VG3; LCSC C136723
TP_3.3V2, TP_5V1: TestPoint; TestPoint_Pad_D1.0mm
TP_GND2: TestPoint; TestPoint_Pad_D1.0mm

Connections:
/ADC/AVDD: CS40.2, CS44.2, IC7.6 (VOUT), TP_5V1.1 (1_1); also elsewhere on the board
/ADC/DVDD: CS33.2, CS34.1, IC5.1 (OUT_1), IC5.2 (OUT_2), R33.1, TP_3.3V2.1 (1_1); also elsewhere on the board
/Power_battery/Bat+: C9.2, IC2.5 (BAT), J4.2, Q1.3 (D)
/Power_battery/non_reg_in: CS31.1, CS41.1, CS43.1, IC5.7 (EN), IC5.9 (IN_1), IC5.10 (IN_2), IC7.4 (OUTDIS), IC7.5 (EN), IC7.7 (VIN), JP1.3 (B), S1.2; also elsewhere on the board
/Vbus: C8.1, D1.2 (A), D2.2 (A), IC2.4 (VCC), IC2.8 (CE), Q1.1 (G), R17.2; also elsewhere on the board
GND: C1.1, C8.2, C9.1, CS31.2, CS32.2, CS34.2, CS40.1, CS41.2, CS43.2, CS44.1, IC2.1 (TEMP), IC2.3 (GND), IC2.9 (EPAD), IC5.4 (GND_1), IC5.6 (SS_CTRL), IC5.11 (GND_2), IC7.8 (GND_1), IC7.9 (GND_2), J4.1, JP1.1 (A), R7.2, R17.1, R32.2, TP_GND2.1 (1_1); also elsewhere on the board
unnamed: C1.2, D1.1 (K), Q1.2 (S), S1.3
unnamed: D2.1 (K), R6.1
unnamed: IC2.7 (CHRG), R6.2
unnamed: IC2.2 (PROG), R7.1
unnamed: CS33.1, IC5.3 (FB), R32.1, R33.2
unnamed: CS32.1, IC5.8 (NR/SS)
unnamed: CCH1.1, IC7.3 (C1+)
unnamed: CCH1.2, IC7.2 (C1-)
unnamed: IC7.1 (PFM), JP1.2 (C)

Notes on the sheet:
R1 = (Vout/0,8 - 1) * R2
PFM disabled for noise reduction
Input Switch
Battery Charger
LDO
5V Charge Pump
Integrated Polarity Protection
Shottky SS34 BAT60B DSK34
